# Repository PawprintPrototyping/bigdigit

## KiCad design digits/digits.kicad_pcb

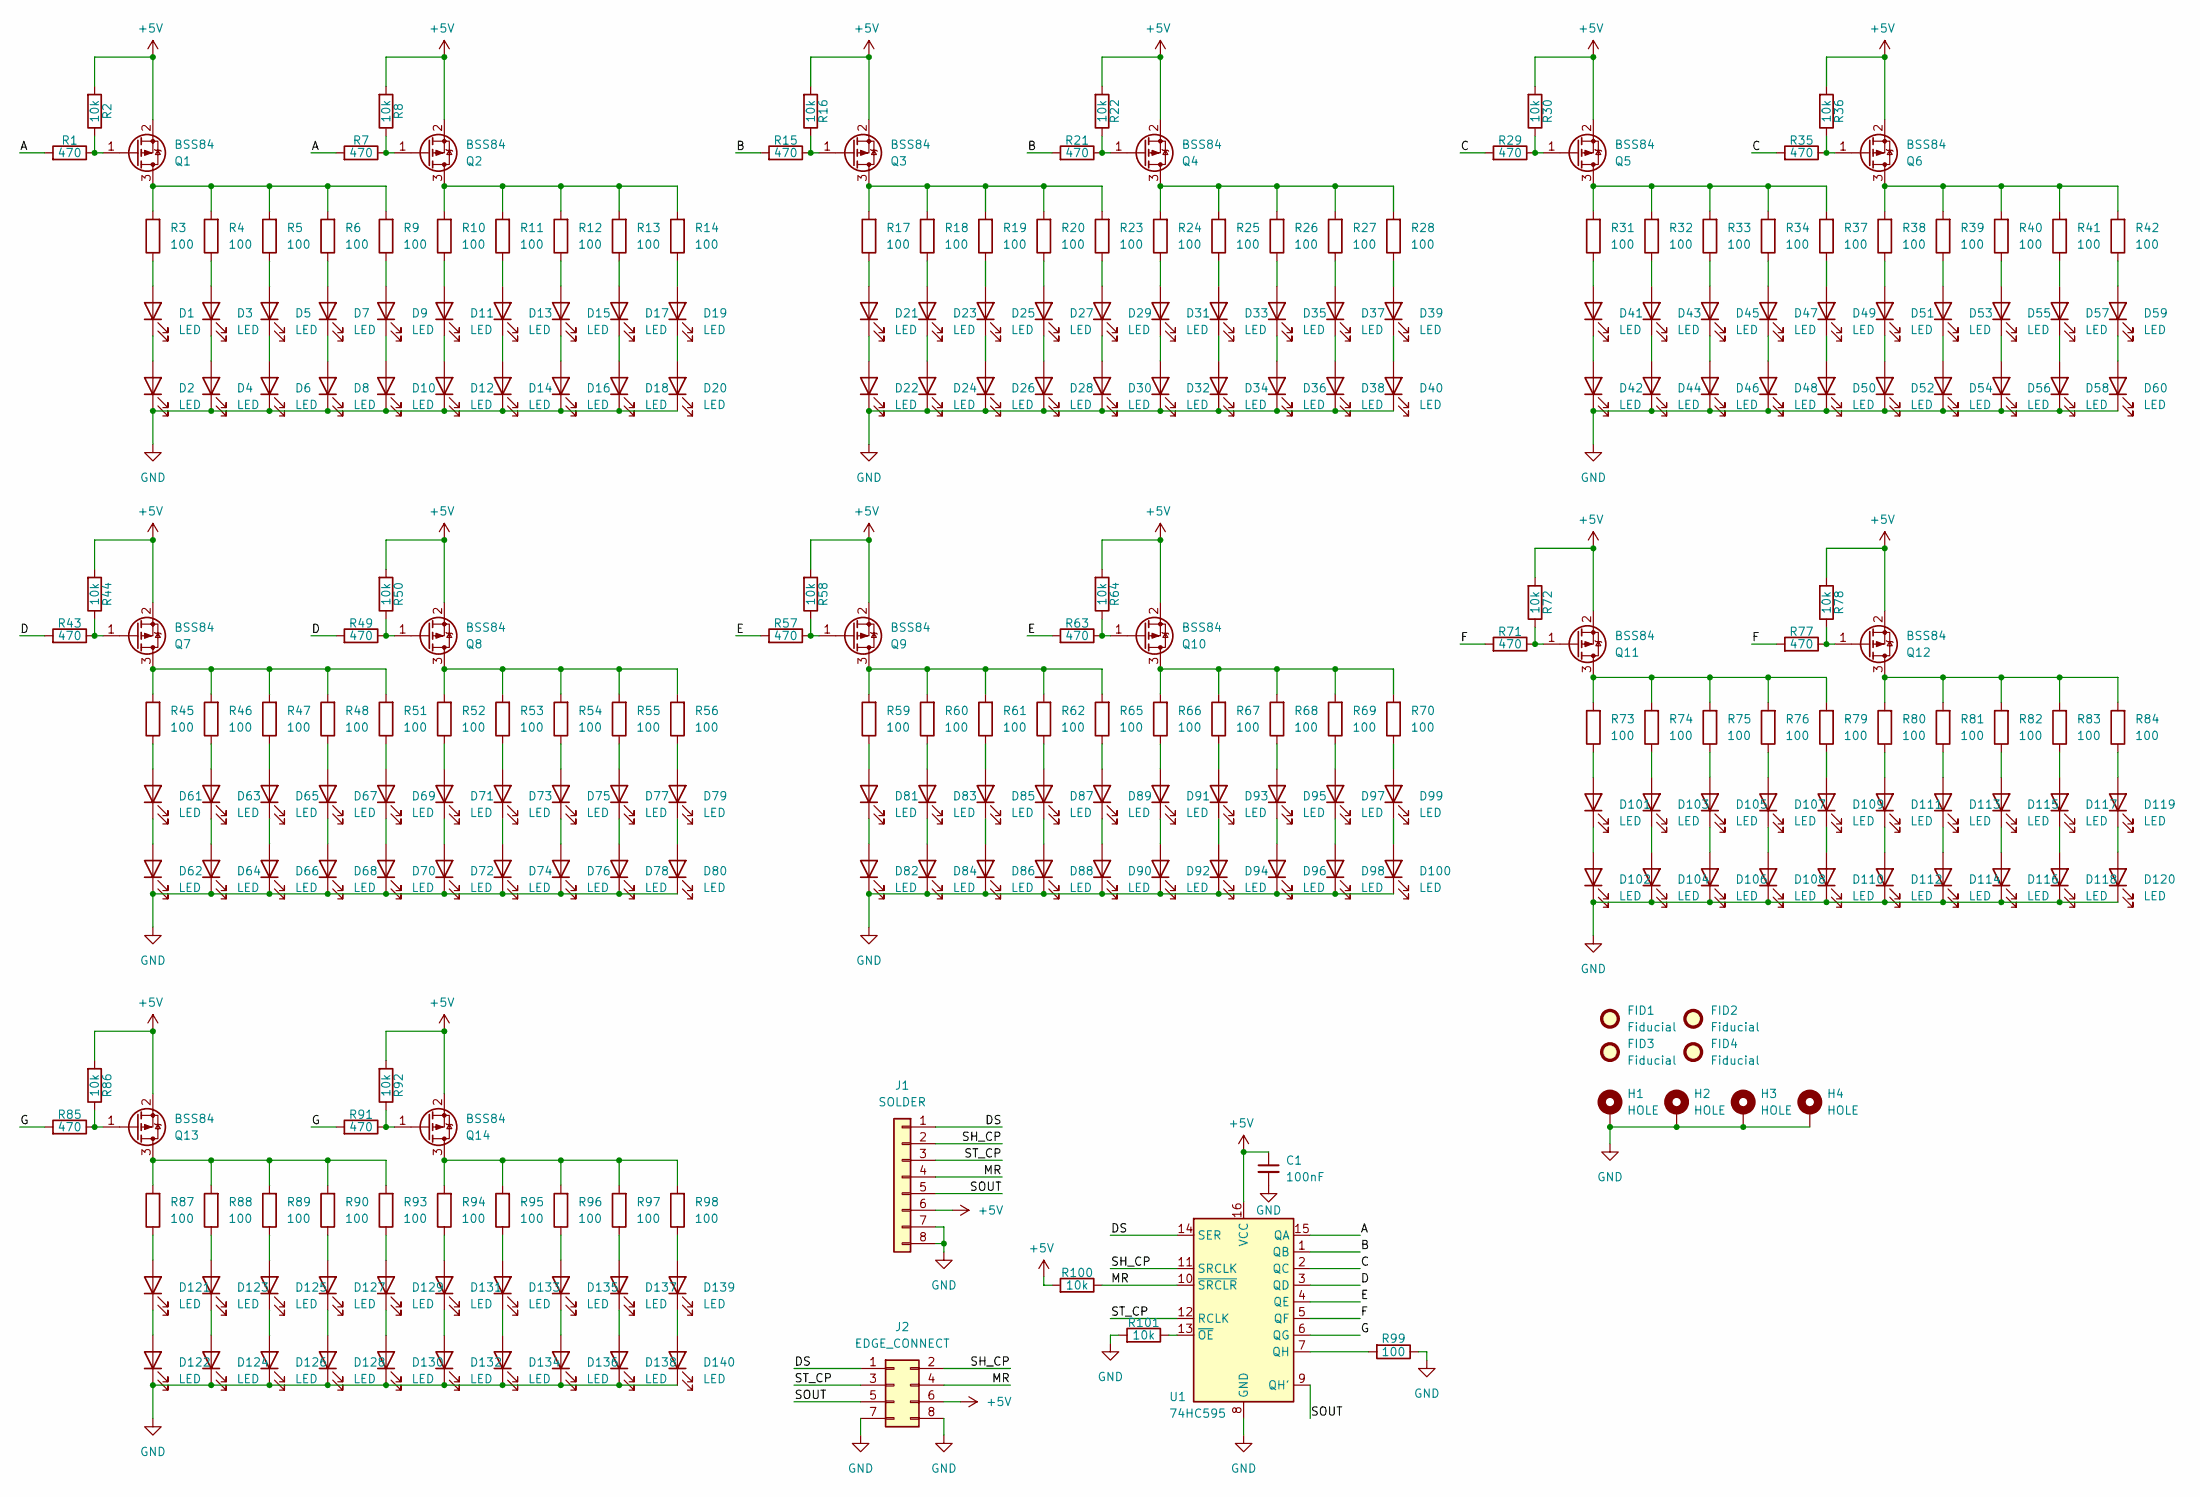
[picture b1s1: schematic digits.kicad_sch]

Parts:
C1: 100nF; C_0603_1608Metric
D1, D2, D3, D4, D5, D6, D7, D8, D9, D10, D11, D12, D13, D14, D15, D16, D17, D18, D19, D20, D21, D22, D23, D24, D25, D26, D27, D28, D29, D30, D31, D32, D33, D34, D35, D36, D37, D38, D39, D40, D41, D42, D43, D44, D45, D46, D47, D48, D49, D50, D51, D52, D53, D54, D55, D56, D57, D58, D59, D60, D61, D62, D63, D64, D65, D66, D67, D68, D69, D70, D71, D72, D73, D74, D75, D76, D77, D78, D79, D80, D81, D82, D83, D84, D85, D86, D87, D88, D89, D90, D91, D92, D93, D94, D95, D96, D97, D98, D99, D100, D101, D102, D103, D104, D105, D106, D107, D108, D109, D110, D111, D112, D113, D114, D115, D116, D117, D118, D119, D120, D121, D122, D123, D124, D125, D126, D127, D128, D129, D130, D131, D132, D133, D134, D135, D136, D137, D138, D139, D140: LED; LED_0603_1608Metric
FID1, FID2, FID3, FID4: Fiducial; Fiducial_1mm_Mask3mm
H1, H2, H3, H4: HOLE; MountingHole_3.2mm_M3_Pad_Via
J1: SOLDER; PinHeader_1x08_P2.54mm_Vertical
J2: EDGE_CONNECT; PinHeader_2x04_P2.54mm_Horizontal
Q1, Q2, Q3, Q4, Q5, Q6, Q7, Q8, Q9, Q10, Q11, Q12, Q13, Q14: BSS84; SOT-23
R1, R7, R15, R21, R29, R35, R43, R49, R57, R63, R71, R77, R85, R91: 470; R_0603_1608Metric_Pad0.98x0.95mm_HandSolder
R2, R8, R16, R22, R30, R36, R44, R50, R58, R64, R72, R78, R86, R92, R100, R101: 10k; R_0603_1608Metric_Pad0.98x0.95mm_HandSolder
R3, R4, R5, R6, R9, R10, R11, R12, R13, R14, R17, R18, R19, R20, R23, R24, R25, R26, R27, R28, R31, R32, R33, R34, R37, R38, R39, R40, R41, R42, R45, R46, R47, R48, R51, R52, R53, R54, R55, R56, R59, R60, R61, R62, R65, R66, R67, R68, R69, R70, R73, R74, R75, R76, R79, R80, R81, R82, R83, R84, R87, R88, R89, R90, R93, R94, R95, R96, R97, R98, R99: 100; R_0603_1608Metric_Pad0.98x0.95mm_HandSolder
U1: 74HC595; SOP-16_3.9x9.9mm_P1.27mm

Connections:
+5V: C1.1, J1.6, J2.6, Q1.2 (S), Q2.2 (S), Q3.2 (S), Q4.2 (S), Q5.2 (S), Q6.2 (S), Q7.2 (S), Q8.2 (S), Q9.2 (S), Q10.2 (S), Q11.2 (S), Q12.2 (S), Q13.2 (S), Q14.2 (S), R2.2, R8.2, R16.2, R22.2, R30.2, R36.2, R44.2, R50.2, R58.2, R64.2, R72.2, R78.2, R86.2, R92.2, R100.2, U1.16 (VCC); also elsewhere on the board
/A: R1.2, R7.2, U1.15 (QA)
/B: R15.2, R21.2, U1.1 (QB)
/C: R29.2, R35.2, U1.2 (QC)
/D: R43.2, R49.2, U1.3 (QD)
/DS: J1.1, J2.1, U1.14 (SER)
/E: R57.2, R63.2, U1.4 (QE)
/F: R71.2, R77.2, U1.5 (QF)
/G: R85.2, R91.2, U1.6 (QG)
/MR: J1.4, J2.4, R100.1, U1.10 (~SRCLR)
/SH_CP: J1.2, J2.2, U1.11 (SRCLK)
/SOUT: J1.5, J2.5, U1.9 (QH')
/ST_CP: J1.3, J2.3, U1.12 (RCLK)
GND: C1.2, D2.1 (K), D4.1 (K), D6.1 (K), D8.1 (K), D10.1 (K), D12.1 (K), D14.1 (K), D16.1 (K), D18.1 (K), D20.1 (K), D22.1 (K), D24.1 (K), D26.1 (K), D28.1 (K), D30.1 (K), D32.1 (K), D34.1 (K), D36.1 (K), D38.1 (K), D40.1 (K), D42.1 (K), D44.1 (K), D46.1 (K), D48.1 (K), D50.1 (K), D52.1 (K), D54.1 (K), D56.1 (K), D58.1 (K), D60.1 (K), D62.1 (K), D64.1 (K), D66.1 (K), D68.1 (K), D70.1 (K), D72.1 (K), D74.1 (K), D76.1 (K), D78.1 (K), D80.1 (K), D82.1 (K), D84.1 (K), D86.1 (K), D88.1 (K), D90.1 (K), D92.1 (K), D94.1 (K), D96.1 (K), D98.1 (K), D100.1 (K), D102.1 (K), D104.1 (K), D106.1 (K), D108.1 (K), D110.1 (K), D112.1 (K), D114.1 (K), D116.1 (K), D118.1 (K), D120.1 (K), D122.1 (K), D124.1 (K), D126.1 (K), D128.1 (K), D130.1 (K), D132.1 (K), D134.1 (K), D136.1 (K), D138.1 (K), D140.1 (K), H1.1, H2.1, H3.1, H4.1, J1.7, J1.8, J2.7, J2.8, R99.1, R101.2, U1.8 (GND); also elsewhere on the board
unnamed: D1.2 (A), R3.1
unnamed: D1.1 (K), D2.2 (A)
unnamed: D3.2 (A), R4.1
unnamed: D3.1 (K), D4.2 (A)
unnamed: D5.2 (A), R5.1
unnamed: D5.1 (K), D6.2 (A)
unnamed: D7.2 (A), R6.1
unnamed: D7.1 (K), D8.2 (A)
unnamed: D9.2 (A), R9.1
unnamed: D9.1 (K), D10.2 (A)
unnamed: D11.2 (A), R10.1
unnamed: D11.1 (K), D12.2 (A)
unnamed: D13.2 (A), R11.1
unnamed: D13.1 (K), D14.2 (A)
unnamed: D15.2 (A), R12.1
unnamed: D15.1 (K), D16.2 (A)
unnamed: D17.2 (A), R13.1
unnamed: D17.1 (K), D18.2 (A)
unnamed: D19.2 (A), R14.1
unnamed: D19.1 (K), D20.2 (A)
unnamed: D21.2 (A), R17.1
unnamed: D21.1 (K), D22.2 (A)
unnamed: D23.2 (A), R18.1
unnamed: D23.1 (K), D24.2 (A)
unnamed: D25.2 (A), R19.1
unnamed: D25.1 (K), D26.2 (A)
unnamed: D27.2 (A), R20.1
unnamed: D27.1 (K), D28.2 (A)
unnamed: D29.2 (A), R23.1
unnamed: D29.1 (K), D30.2 (A)
unnamed: D31.2 (A), R24.1
unnamed: D31.1 (K), D32.2 (A)
unnamed: D33.2 (A), R25.1
unnamed: D33.1 (K), D34.2 (A)
unnamed: D35.2 (A), R26.1
unnamed: D35.1 (K), D36.2 (A)
unnamed: D37.2 (A), R27.1
unnamed: D37.1 (K), D38.2 (A)
unnamed: D39.2 (A), R28.1
unnamed: D39.1 (K), D40.2 (A)
unnamed: D41.2 (A), R31.1
unnamed: D41.1 (K), D42.2 (A)
unnamed: D43.2 (A), R32.1
unnamed: D43.1 (K), D44.2 (A)
unnamed: D45.2 (A), R33.1
unnamed: D45.1 (K), D46.2 (A)
unnamed: D47.2 (A), R34.1
unnamed: D47.1 (K), D48.2 (A)
unnamed: D49.2 (A), R37.1
unnamed: D49.1 (K), D50.2 (A)
unnamed: D51.2 (A), R38.1
unnamed: D51.1 (K), D52.2 (A)
unnamed: D53.2 (A), R39.1
unnamed: D53.1 (K), D54.2 (A)
unnamed: D55.2 (A), R40.1
unnamed: D55.1 (K), D56.2 (A)
unnamed: D57.2 (A), R41.1
unnamed: D57.1 (K), D58.2 (A)
unnamed: D59.2 (A), R42.1
unnamed: D59.1 (K), D60.2 (A)
unnamed: D61.2 (A), R45.1
unnamed: D61.1 (K), D62.2 (A)
unnamed: D63.2 (A), R46.1
unnamed: D63.1 (K), D64.2 (A)
unnamed: D65.2 (A), R47.1
unnamed: D65.1 (K), D66.2 (A)
unnamed: D67.2 (A), R48.1
unnamed: D67.1 (K), D68.2 (A)
unnamed: D69.2 (A), R51.1
unnamed: D69.1 (K), D70.2 (A)
unnamed: D71.2 (A), R52.1
unnamed: D71.1 (K), D72.2 (A)
unnamed: D73.2 (A), R53.1
unnamed: D73.1 (K), D74.2 (A)
unnamed: D75.2 (A), R54.1
unnamed: D75.1 (K), D76.2 (A)
unnamed: D77.2 (A), R55.1
unnamed: D77.1 (K), D78.2 (A)
unnamed: D79.2 (A), R56.1
unnamed: D79.1 (K), D80.2 (A)
unnamed: D81.2 (A), R59.1
unnamed: D81.1 (K), D82.2 (A)
unnamed: D83.2 (A), R60.1
unnamed: D83.1 (K), D84.2 (A)
unnamed: D85.2 (A), R61.1
unnamed: D85.1 (K), D86.2 (A)
unnamed: D87.2 (A), R62.1
unnamed: D87.1 (K), D88.2 (A)
unnamed: D89.2 (A), R65.1
unnamed: D89.1 (K), D90.2 (A)
unnamed: D91.2 (A), R66.1
unnamed: D91.1 (K), D92.2 (A)
unnamed: D93.2 (A), R67.1
unnamed: D93.1 (K), D94.2 (A)
unnamed: D95.2 (A), R68.1
unnamed: D95.1 (K), D96.2 (A)
unnamed: D97.2 (A), R69.1
unnamed: D97.1 (K), D98.2 (A)
unnamed: D99.2 (A), R70.1
unnamed: D99.1 (K), D100.2 (A)
unnamed: D101.2 (A), R73.1
unnamed: D101.1 (K), D102.2 (A)
unnamed: D103.2 (A), R74.1
unnamed: D103.1 (K), D104.2 (A)
unnamed: D105.2 (A), R75.1
unnamed: D105.1 (K), D106.2 (A)
unnamed: D107.2 (A), R76.1
unnamed: D107.1 (K), D108.2 (A)
unnamed: D109.2 (A), R79.1
unnamed: D109.1 (K), D110.2 (A)
unnamed: D111.2 (A), R80.1
unnamed: D111.1 (K), D112.2 (A)
unnamed: D113.2 (A), R81.1
unnamed: D113.1 (K), D114.2 (A)
unnamed: D115.2 (A), R82.1
unnamed: D115.1 (K), D116.2 (A)
unnamed: D117.2 (A), R83.1
unnamed: D117.1 (K), D118.2 (A)
unnamed: D119.2 (A), R84.1
unnamed: D119.1 (K), D120.2 (A)
unnamed: D121.2 (A), R87.1
unnamed: D121.1 (K), D122.2 (A)
unnamed: D123.2 (A), R88.1
unnamed: D123.1 (K), D124.2 (A)
unnamed: D125.2 (A), R89.1
unnamed: D125.1 (K), D126.2 (A)
unnamed: D127.2 (A), R90.1
unnamed: D127.1 (K), D128.2 (A)
unnamed: D129.2 (A), R93.1
unnamed: D129.1 (K), D130.2 (A)
unnamed: D131.2 (A), R94.1
unnamed: D131.1 (K), D132.2 (A)
unnamed: D133.2 (A), R95.1
unnamed: D133.1 (K), D134.2 (A)
unnamed: D135.2 (A), R96.1
unnamed: D135.1 (K), D136.2 (A)
unnamed: D137.2 (A), R97.1
unnamed: D137.1 (K), D138.2 (A)
unnamed: D139.2 (A), R98.1
unnamed: D139.1 (K), D140.2 (A)
unnamed: Q1.3 (D), R3.2, R4.2, R5.2, R6.2, R9.2
unnamed: Q1.1 (G), R1.1, R2.1
unnamed: Q2.3 (D), R10.2, R11.2, R12.2, R13.2, R14.2
unnamed: Q2.1 (G), R7.1, R8.1
unnamed: Q3.3 (D), R17.2, R18.2, R19.2, R20.2, R23.2
unnamed: Q3.1 (G), R15.1, R16.1
unnamed: Q4.3 (D), R24.2, R25.2, R26.2, R27.2, R28.2
unnamed: Q4.1 (G), R21.1, R22.1
unnamed: Q5.3 (D), R31.2, R32.2, R33.2, R34.2, R37.2
unnamed: Q5.1 (G), R29.1, R30.1
unnamed: Q6.3 (D), R38.2, R39.2, R40.2, R41.2, R42.2
unnamed: Q6.1 (G), R35.1, R36.1
unnamed: Q7.3 (D), R45.2, R46.2, R47.2, R48.2, R51.2
unnamed: Q7.1 (G), R43.1, R44.1
unnamed: Q8.3 (D), R52.2, R53.2, R54.2, R55.2, R56.2
unnamed: Q8.1 (G), R49.1, R50.1
unnamed: Q9.3 (D), R59.2, R60.2, R61.2, R62.2, R65.2
unnamed: Q9.1 (G), R57.1, R58.1
unnamed: Q10.3 (D), R66.2, R67.2, R68.2, R69.2, R70.2
unnamed: Q10.1 (G), R63.1, R64.1
unnamed: Q11.3 (D), R73.2, R74.2, R75.2, R76.2, R79.2
unnamed: Q11.1 (G), R71.1, R72.1
unnamed: Q12.3 (D), R80.2, R81.2, R82.2, R83.2, R84.2
unnamed: Q12.1 (G), R77.1, R78.1
unnamed: Q13.3 (D), R87.2, R88.2, R89.2, R90.2, R93.2
unnamed: Q13.1 (G), R85.1, R86.1
unnamed: Q14.3 (D), R94.2, R95.2, R96.2, R97.2, R98.2
unnamed: Q14.1 (G), R91.1, R92.1
unnamed: R99.2, U1.7 (QH)
unnamed: R101.1, U1.13 (~OE)

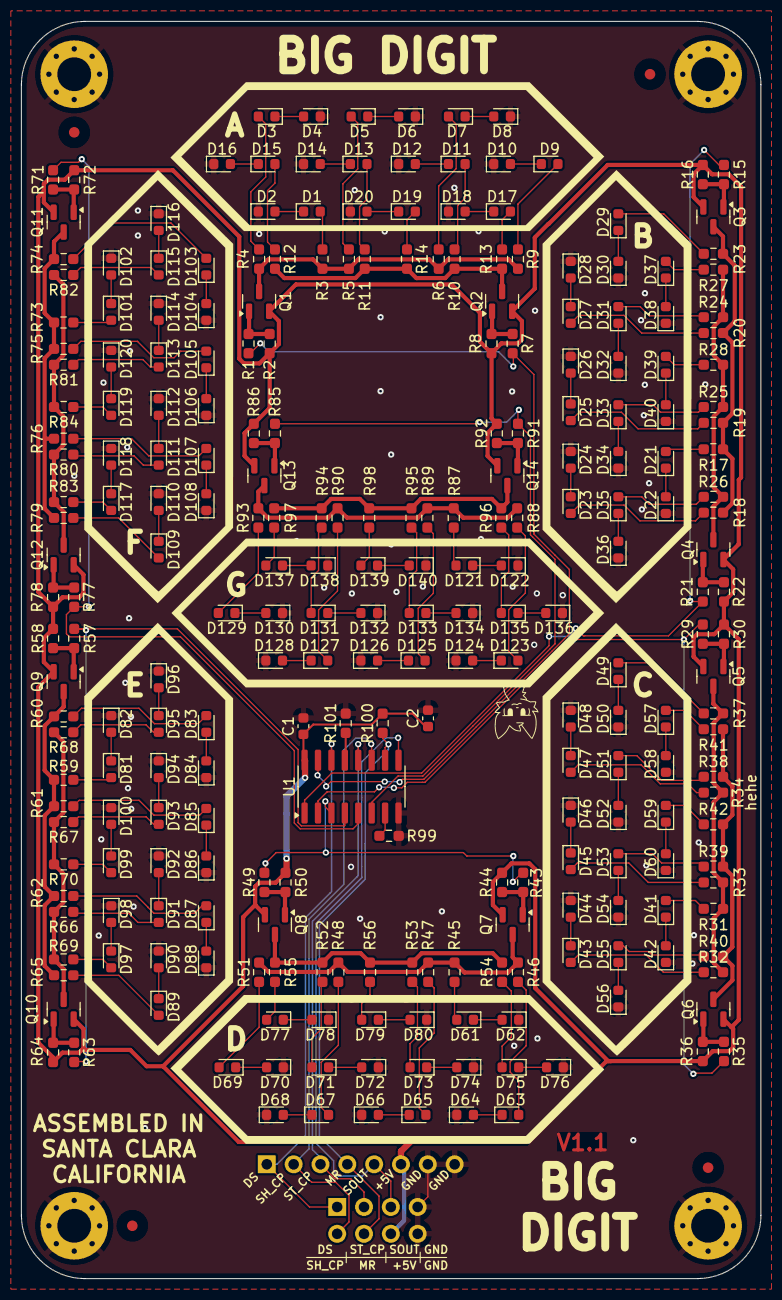
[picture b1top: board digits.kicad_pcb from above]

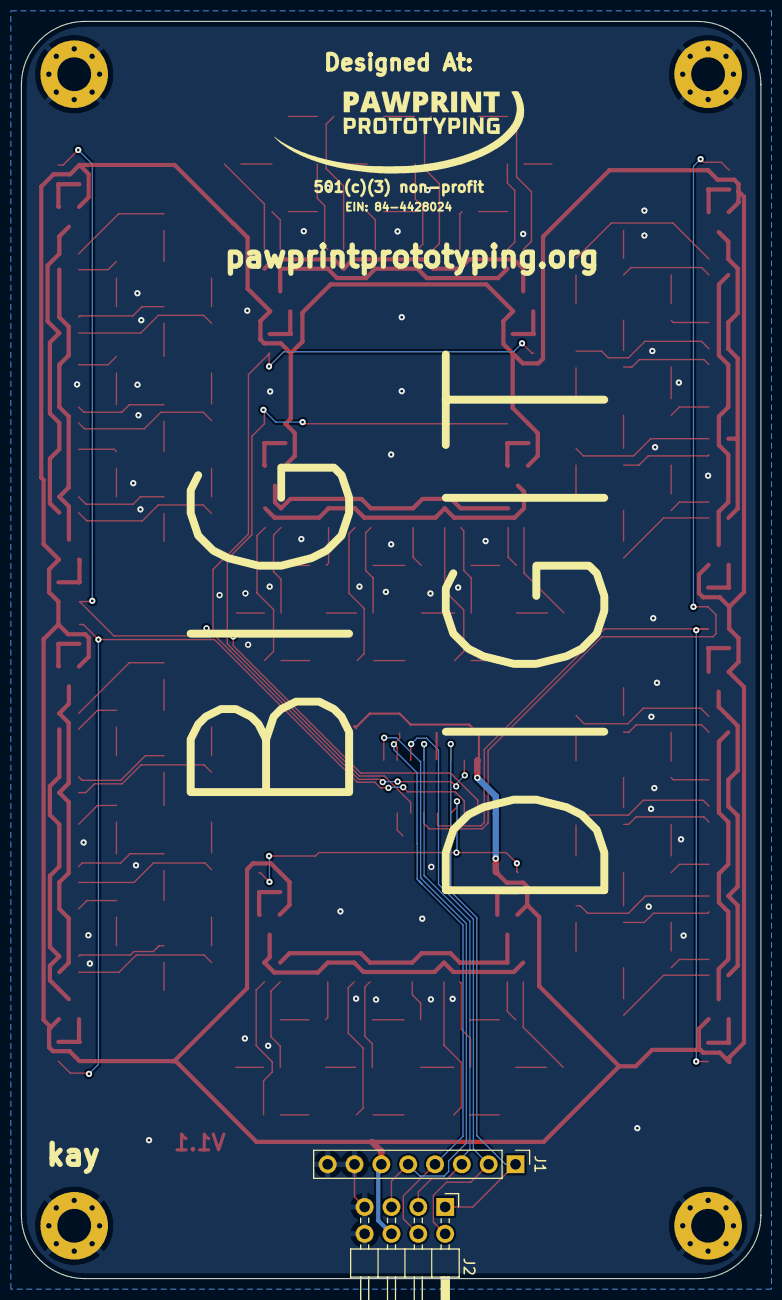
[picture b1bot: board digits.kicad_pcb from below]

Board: 2 copper layers, 70.0 x 119.0 mm, 268 parts (2 on the bottom side), 184 nets.

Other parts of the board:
C2: 100nF; C_0603_1608Metric

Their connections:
+5V: C2.1; also elsewhere on the board
GND: C2.2; also elsewhere on the board

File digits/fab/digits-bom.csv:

"Id";"Designator";"Footprint";"Quantity";"Designation";"Supplier and ref";
1;"R40,R97,R54,R75,R51,R6,R11,R45,R52,R70,R65,R61,R60,R83,R28,R32,R87,R56,R27,R95,R66,R33,R12,R76,R10,R5,R46,R79,R48,R3,R23,R84,R93,R55,R18,R42,R39,R80,R38,R96,R25,R19,R62,R59,R82,R73,R94,R14,R41,R47,R34,R69,R67,R20,R17,R74,R31,R26,R37,R81,R13,R24,R53,R98,R90,R88,R4,R89,R9,R99,R68";"R_0603_1608Metric_Pad0.98x0.95mm_HandSolder";71;"100";;;
2;"D61,D9,D19,D129,D134,D84,D130,D131,D77,D105,D126,D10,D117,D44,D114,D34,D18,D89,D43,D112,D16,D91,D69,D62,D132,D20,D55,D6,D137,D25,D74,D50,D104,D78,D37,D31,D125,D39,D86,D133,D38,D47,D110,D13,D101,D67,D12,D59,D53,D58,D42,D27,D5,D119,D3,D57,D100,D120,D96,D35,D33,D64,D26,D122,D90,D45,D121,D108,D88,D76,D49,D71,D138,D63,D51,D102,D75,D94,D127,D29,D103,D93,D72,D95,D73,D52,D4,D99,D81,D40,D140,D109,D106,D82,D28,D111,D41,D60,D8,D30,D98,D14,D7,D65,D54,D128,D66,D79,D70,D15,D87,D92,D97,D68,D123,D32,D80,D46,D56,D17,D113,D85,D36,D2,D107,D136,D116,D48,D135,D124,D22,D1,D11,D24,D115,D139,D21,D23,D83,D118";"LED_0603_1608Metric";140;"LED";;;
3;"R36,R72,R8,R100,R92,R30,R44,R101,R58,R50,R22,R86,R2,R16,R78,R64";"R_0603_1608Metric_Pad0.98x0.95mm_HandSolder";16;"10k";;;
4;"R91,R77,R49,R21,R35,R29,R43,R57,R7,R71,R15,R63,R85,R1";"R_0603_1608Metric_Pad0.98x0.95mm_HandSolder";14;"470";;;
5;"U1";"SOP-16_3.9x9.9mm_P1.27mm";1;"74HC595";;;
6;"C2,C1";"C_0603_1608Metric";2;"100nF";;;
7;"Q1,Q2,Q9,Q4,Q10,Q7,Q6,Q14,Q8,Q11,Q3,Q5,Q12,Q13";"SOT-23";14;"BSS84";;;
8;"U2";"TSSOP-20_4.4x5mm_P0.5mm";1;"74AHC244";;;
9;"J1";"PinHeader_1x08_P2.54mm_Vertical";1;"SOLDER";;;
10;"J2";"PinHeader_2x04_P2.54mm_Horizontal";1;"EDGE_CONNECT";;;
11;"REF**";"logo_designed_at";1;"logo_designed_at";;;

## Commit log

2024-11-04 first
2024-11-06 Added fiducials, fixed typo on the connector, added the correct origin, added a version number
2024-12-08 didn't even need that part
